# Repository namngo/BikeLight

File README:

Led controller chip:
https://www.monolithicpower.com/en/documentview/productdocument/index/version/2/document_type/Datasheet/lang/en/sku/MP2410/document_id/2079
https://www.monolithicpower.com/en/documentview/productdocument/index/version/2/document_type/Datasheet/lang/en/sku/EV2410-J-00A/document_id/2797/

## Part links

### Screens
* Screen: https://www.aliexpress.us/item/3256804050802693.html?spm=a2g0o.order_list.order_list_main.81.6dc41802Oe7kPv&gatewayAdapt=glo2usa#nav-specification

### ESP32

#### Esp32 super mini

* ESP32 module: https://www.aliexpress.us/item/3256810393697250.html?spm=a2g0o.order_list.order_list_main.29.6dc41802Oe7kPv&gatewayAdapt=glo2usa#nav-specification

```
Product parameter

Powerful CPU: ESP32-S3, 32-bit RISC-V single-core processor, running at up to 160 MHz

WiFi: 802.11b/g/n protocol, 2.4GhHz, support Station mode, SoftAP mode, SoftAP+Station mode, hybrid mode

Bluetooth: Bluetooth 5.0

Ultra-low power consumption: deep sleep power consumption of about 43μA

Rich board resources: 400KB SRAM, 384KB ROM built-in 4Mflash.

Chip model: ESP32S3FH4R2

Ultra-small size: As small as the thumb (22.52x18mm) classic shape, suitable for wearables and small projects

Reliable security features: Encryption hardware accelerators that support AES-128/256, hashing, RSA, HMAC, digital signatures, and secure startup

Rich interface: 1xI2C, 1xSPI, 2xUART, 11xGPIO(PWM), 4xADC

Onboard RGB, blue LED: common GPIO 48 pin

```

## Research

https://michaelmanning.ca/e-paper-climate-logger/

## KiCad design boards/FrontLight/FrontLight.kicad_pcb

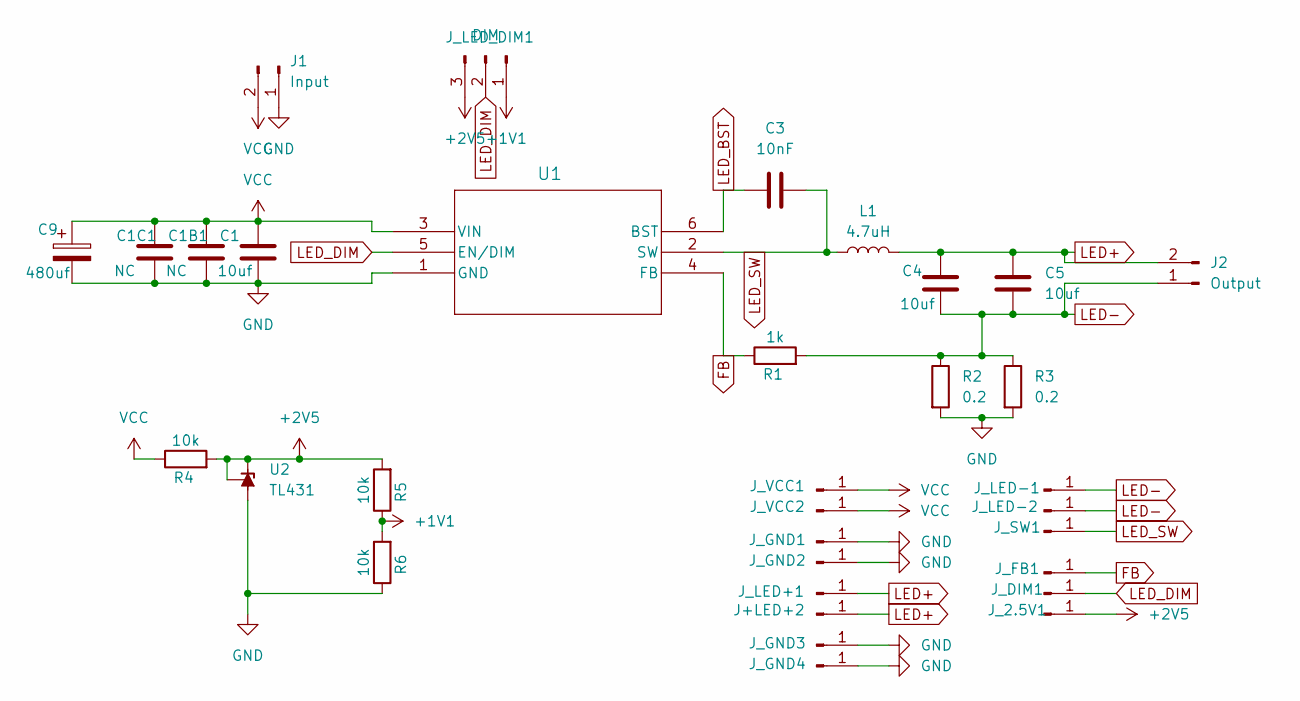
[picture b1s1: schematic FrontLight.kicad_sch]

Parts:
C1, C4, C5: 10uf; C_1210_3225Metric_Pad1.33x2.70mm_HandSolder
C1B1: NC; C_1210_3225Metric_Pad1.33x2.70mm_HandSolder
C1C1: NC; C_0805_2012Metric_Pad1.18x1.45mm_HandSolder
C3: 10nF; C_0805_2012Metric_Pad1.18x1.45mm_HandSolder
C9: 480uf; CP_Elec_10x10
J1: Input; PinHeader_1x02_P2.54mm_Vertical
J2: Output; PinHeader_1x02_P2.54mm_Vertical
J+LED+2: LED+; PinHeader_1x01_P2.54mm_Vertical
J_2.5V1: 3.3v; PinHeader_1x01_P2.54mm_Vertical
J_DIM1: DIM; PinHeader_1x01_P2.54mm_Vertical
J_FB1: FB; PinHeader_1x01_P2.54mm_Vertical
J_GND1, J_GND2, J_GND3, J_GND4: GND; PinHeader_1x01_P2.54mm_Vertical
J_LED+1: LED+; PinHeader_1x01_P2.54mm_Vertical
J_LED-1, J_LED-2: LED-; PinHeader_1x01_P2.54mm_Vertical
J_LED_DIM1: DIM; PinHeader_1x03_P2.54mm_Vertical
J_SW1: SW; PinHeader_1x01_P2.54mm_Vertical
J_VCC1, J_VCC2: VCC; PinHeader_1x01_P2.54mm_Vertical
L1: 4.7uH; L_Bourns_SRR1260
R1: 1k; R_0805_2012Metric_Pad1.20x1.40mm_HandSolder
R2, R3: 0.2; R_1206_3216Metric_Pad1.30x1.75mm_HandSolder
R4, R5, R6: 10k; R_0805_2012Metric_Pad1.20x1.40mm_HandSolder
U1: MP2410GJ-P; TSOT23-6_MP2410_MNP
U2: TL431; SOT-23

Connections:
+1V1: J_LED_DIM1.1, R5.1, R6.2
+2V5: J_2.5V1.1, J_LED_DIM1.3, R4.2, R5.2, U2.1 (K), U2.2 (REF)
FB: J_FB1.1, R1.1, U1.4 (FB)
GND: C1.2, C1B1.2, C1C1.2, C9.2, J1.1, J_GND1.1, J_GND2.1, J_GND3.1, J_GND4.1, R2.2, R3.2, R6.1, U1.1 (GND), U2.3 (A)
LED+: C4.1, C5.1, J2.2, J+LED+2.1, J_LED+1.1, L1.2
LED-: C4.2, C5.2, J2.1, J_LED-1.1, J_LED-2.1, R1.2, R2.1, R3.1
LED_BST: C3.2, U1.6 (BST)
LED_DIM: J_DIM1.1, J_LED_DIM1.2, U1.5 (EN/DIM)
LED_SW: C3.1, J_SW1.1, L1.1, U1.2 (SW)
VCC: C1.1, C1B1.1, C1C1.1, C9.1, J1.2, J_VCC1.1, J_VCC2.1, R4.1, U1.3 (VIN)

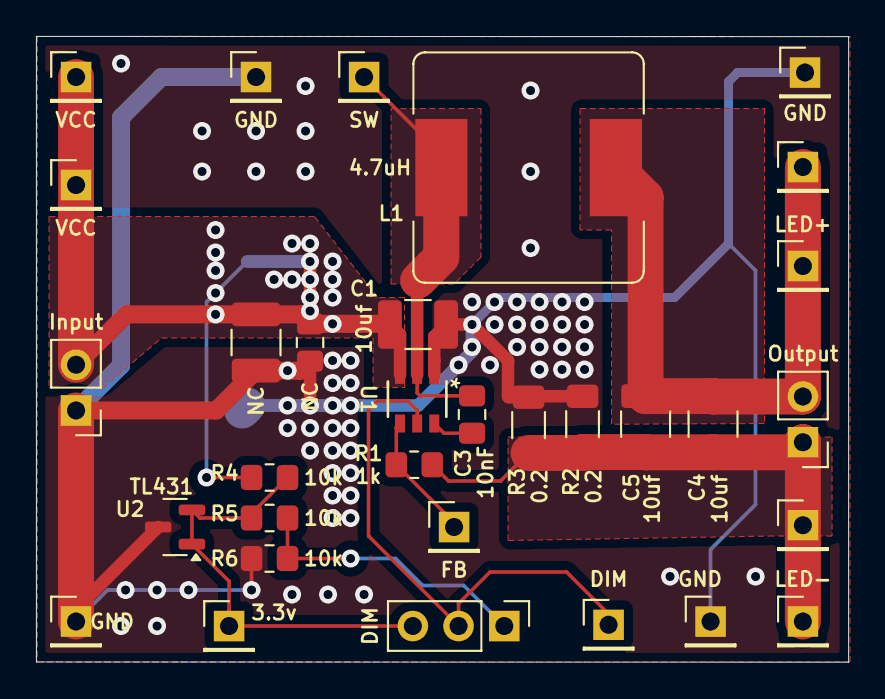
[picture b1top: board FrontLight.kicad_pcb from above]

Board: 2 copper layers, 45.1 x 34.8 mm, 33 parts (1 on the bottom side), 10 nets.

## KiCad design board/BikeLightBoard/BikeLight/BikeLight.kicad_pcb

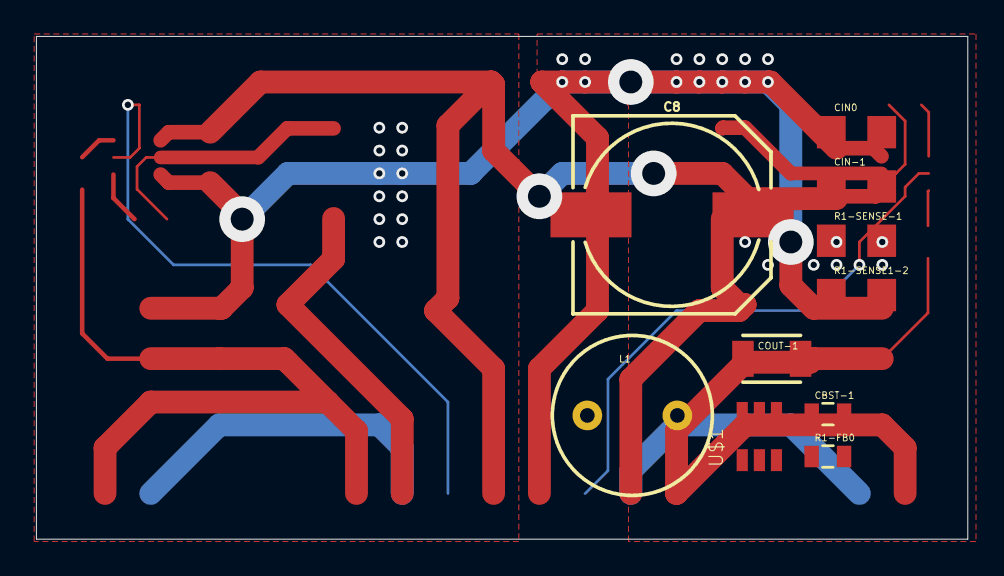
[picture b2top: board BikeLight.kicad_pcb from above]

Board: 2 copper layers, 51.7 x 27.9 mm, 10 parts (0 on the bottom side), 7 nets.

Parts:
C8: 100uF; NIC_10X10.5_CAP
CBST-1: 10nF; 0805
CIN0: 4.7uf; 1206
CIN-1: 4.7uf; 1206
COUT-1: 10uf; 1210
L1: 4.7uf; RLB0912
R1-FB0: 1k; 0805
R1-SENSE1-2: 200mO; 1206
R1-SENSE-1: 100mO; 1206
U$1: MP2410; TSOT23-6

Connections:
+12V: C8.+, CIN0.1, CIN-1.1, U$1.3 (IN)
GND: C8.-, CIN0.2, CIN-1.2, R1-SENSE1-2.2, R1-SENSE-1.2, U$1.1 (GND)
unnamed: COUT-1.1, L1.2
unnamed: COUT-1.2, R1-FB0.2, R1-SENSE1-2.1, R1-SENSE-1.1
unnamed: CBST-1.1, U$1.6 (BST)
unnamed: R1-FB0.1, U$1.4 (FB)
unnamed: CBST-1.2, L1.1, U$1.2 (SW)

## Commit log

2019-11-02 add readme
2019-11-06 finish board
2019-11-06 finishing touch
2020-04-02 library
2020-04-03 arduino settings
2020-04-04 debuging i2c
2020-04-06 sensors working
2020-04-06 try new icm library
2020-04-07 change to new lib
2020-04-07 add new icm lib
2020-04-08 remove 1.8v
2020-04-08 update mpu9250
2020-04-09 use mpu
2020-04-10 change
2020-04-15 stringstream
2020-04-20 esp32
2020-04-20 Try sparkfun dmp
2020-04-20 borderflight mpu9250
2020-04-20 calibrated
2020-04-20 got data
2020-04-20 remove icm20948 files
2020-04-20 add mpu9250 lib
2020-04-20 remove icm code
2025-12-26 esp32 s3
2025-12-29 add kicad board
2025-12-29 add new bike board
2025-12-30 finish working today
2026-01-02 remove old bikeboards
2026-01-02 Revert "remove old bikeboards"
    This reverts commit a9e1404b7c4aa93456804174a9f9b6465af947c2.
2026-01-02 remove old eagle board
2026-01-06 mp2410
2026-01-09 code
2026-01-20 clean up for mp2410
2026-01-20 mp2410 boards
2026-01-20 done basic board
2026-01-20 finish the board
2026-01-20 light
2026-01-22 remove export files
2026-01-22 remove old directoy
2026-01-22 export to pdf
2026-01-27 add parts
2026-02-04 main board
2026-03-05 new board
2026-04-09 add esp32
